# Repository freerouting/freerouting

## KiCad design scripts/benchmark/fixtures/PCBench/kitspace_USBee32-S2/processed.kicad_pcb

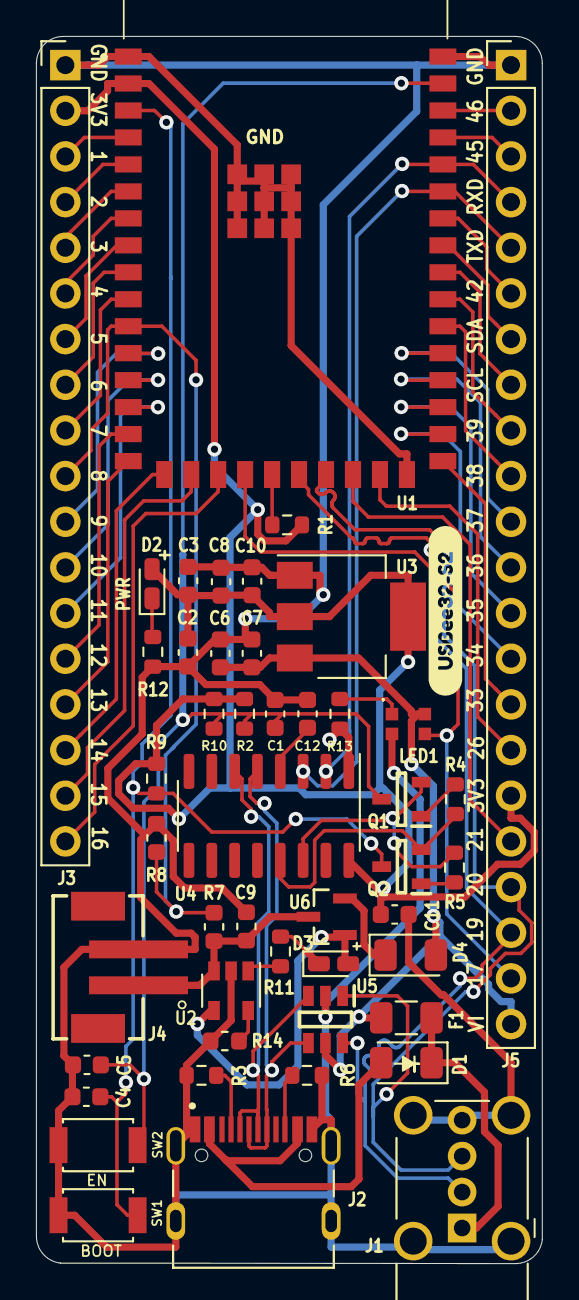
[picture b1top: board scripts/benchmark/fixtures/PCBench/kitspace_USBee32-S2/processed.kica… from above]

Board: 4 copper layers, 28.1 x 68.3 mm, 49 parts (1 on the bottom side), 59 nets.

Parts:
C1, C2, C4, C5, C7, C10, C11, C12: 0.1uF; C_0603_1608Metric
C3, C9: 10uF; C_0603_1608Metric
C6: 10 uF; C_0603_1608Metric
C8: 22 uF; C_0603_1608Metric
D1, D4: 1N5819; D_1206_3216Metric
D2, D3: LED; LED_0603_1608Metric_Castellated
F1: Polyfuse_Small; Fuse_1206_3216Metric
J1: USB_A; USB_A_Wuerth_614004134726_Horizontal
J2: TYPE-C-31-M-12; HRO_TYPE-C-31-M-12
J3: Conn_01x18_Male; PinHeader_1x18_P2.54mm_Vertical
J4: B2B-PH-SM4-TB(LF)(SN); JST_B2B-PH-SM4-TB(LF)(SN)
J5: Conn_01x22_Male; PinHeader_1x22_P2.54mm_Vertical
LED1: WS2812B-2020; WS2812B2020
Q1, Q2: MMBT8050
R1, R2, R4, R5, R9, R10: 10K; R_0603_1608Metric
R3, R6: 5.1K; R_0603_1608Metric
R7, R8: 100k; R_0603_1608Metric
R11, R12, R13: 1k; R_0603_1608Metric
R14: 4.7k; R_0603_1608Metric
SW1, SW2: SW_Push; tactile_smd_switch
U1: ESP32-S2-WROOM-ESP32-S2-WROOM; ESP32S2WROOMM22S2H3200PH3Q0
U2: MCP73831-2-OT; SOT-23-5
U3: AMS1117-3.3; SOT-223-3_TabPin2
U4: CH340C; SOIC-16_3.9x9.9mm_P1.27mm
U5: IP4220CZ6; SOP95P275X110-6N
U6: DMP2305U-7; SOT103P240X110-3N
svg2mod, svg2mod_2: G***; label

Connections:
+3V3: C2.1, C3.1, C8.2, C10.2, C11.1, D2.2, J3.2, J5.17, R1.1, R2.1, R9.2, R10.2, U1.2, U3.2, U4.16
+BATT: C9.1, J4.1, R7.1, U2.3, U6.3
/CC1: J2.A5, R3.1
/CC2: J2.B5, R6.1
/CHIP_PU: C1.1, C5.2, Q1.3, R2.2, R10.1, SW2.2, U1.41
/D1+: J1.3, J5.19, U1.23, U5.1
/D1-: J1.2, J5.20, U1.22, U5.6
/DN1: J2.A7, J2.B7, U4.6, U5.3
/DP1: J2.A6, J2.B6, U4.5, U5.4
/GPIO_0: C4.2, Q2.3, R9.1, SW1.2, U1.3
/GPIO_1: J3.3, U1.4
/GPIO_2: J3.4, U1.5
/GPIO_3: J3.5, U1.6
/GPIO_4: J3.6, U1.7
/GPIO_5: J3.7, U1.8
/GPIO_6: J3.8, U1.9
/GPIO_7: J3.9, U1.10
/GPIO_8: J3.10, R7.2, R8.1, U1.11
/GPIO_9: J3.11, U1.12
/GPIO_10: J3.12, U1.13
/GPIO_11: J3.13, U1.14
/GPIO_12: J3.14, U1.15
/GPIO_13: J3.15, U1.16
/GPIO_14: J3.16, U1.17
/GPIO_15: J3.17, U1.18
/GPIO_16: J3.18, U1.19
/GPIO_17: J5.21, LED1.3, U1.20
/GPIO_18: R1.2, U1.21
/GPIO_21: J5.18, U1.24
/GPIO_26: J5.16, U1.25
/GPIO_33: J5.15, U1.27
/GPIO_34: J5.14, U1.28
/GPIO_35: J5.13, U1.29
/GPIO_36: J5.12, U1.30
/GPIO_37: J5.11, U1.31
/GPIO_38: J5.10, U1.32
/GPIO_39: J5.9, U1.33
/GPIO_40: J5.8, U1.34
/GPIO_41: J5.7, U1.35
/GPIO_42: J5.6, U1.36
/GPIO_45: J5.3, U1.39
/GPIO_46: J5.2, U1.40
/RXD0: J5.4, U1.38, U4.2
/TXD0: J5.5, U1.37, U4.3
/VBUSA: D1.1, F1.2, J1.1
/VBUSC: D1.2, J2.A4B9, J2.B4A9
/VI: C6.2, C7.2, D3.2, D4.2, F1.1, J5.22, LED1.4, U2.4, U3.3, U5.5, U6.1
/~DTR: Q2.2, R4.1, U4.13
/~RTS: Q1.2, R5.1, U4.14
GND: C1.2, C2.2, C3.2, C4.1, C5.1, C6.1, C7.1, C8.1, C9.2, C10.1, C11.2, C12.2, J1.4, J1.5, J2.A1B12, J2.B1A12, J2.S1, J2.S2, J2.S3, J2.S4, J3.1, J4.2, J5.1, LED1.2, R3.2, R6.2, R8.2, R12.2, R13.2, R14.2, SW1.1, SW2.1, U1.1, U1.26, U1.42, U1.43, U1.44, U1.45, U1.46, U1.47, U1.48, U1.49, U1.50, U1.51, U2.2, U3.1, U4.1, U5.2
unnamed: C12.1, U4.4
unnamed: D2.1, R12.1
unnamed: D3.1, R11.1
unnamed: D4.1, U6.2
unnamed: LED1.1, R13.1
unnamed: Q1.1, R4.2
unnamed: Q2.1, R5.2
unnamed: R11.2, U2.1
unnamed: R14.1, U2.5

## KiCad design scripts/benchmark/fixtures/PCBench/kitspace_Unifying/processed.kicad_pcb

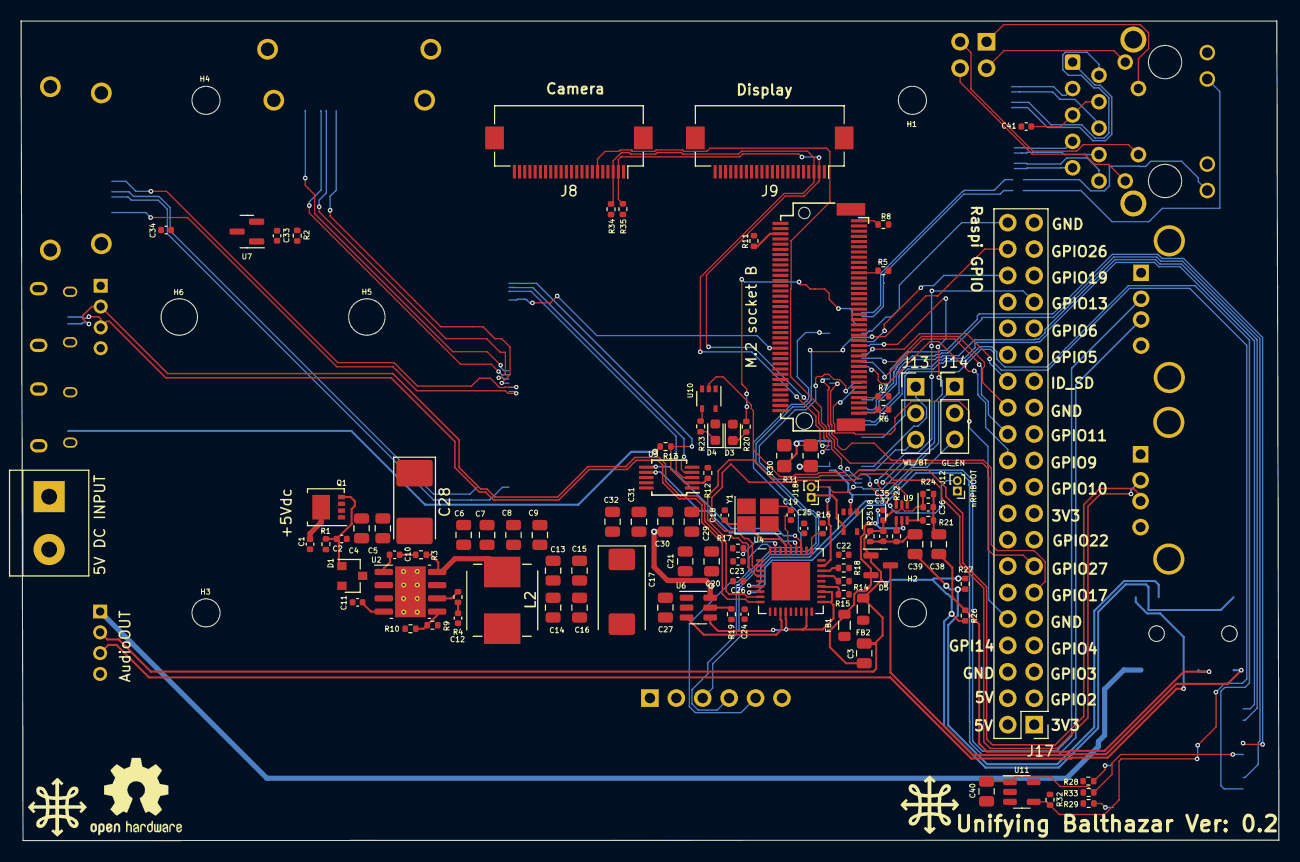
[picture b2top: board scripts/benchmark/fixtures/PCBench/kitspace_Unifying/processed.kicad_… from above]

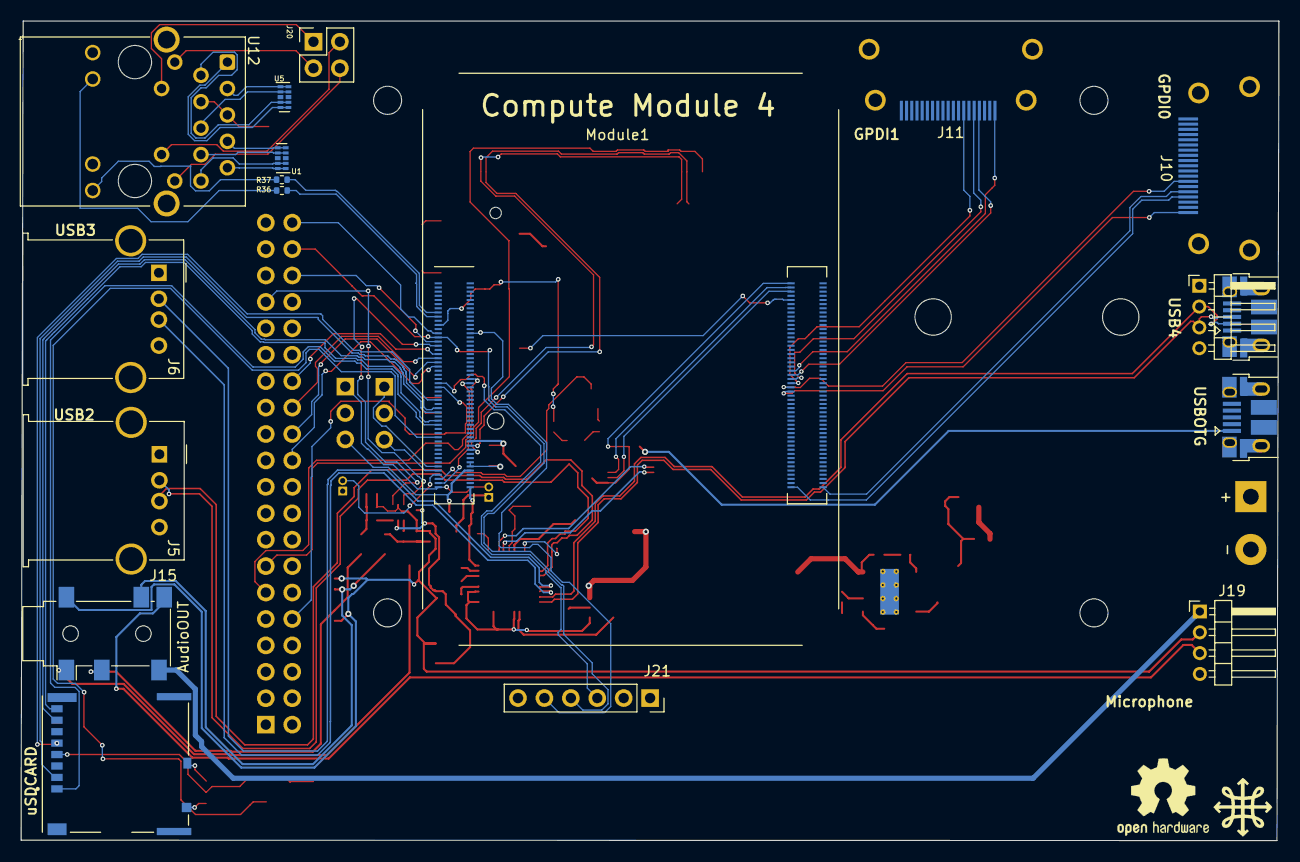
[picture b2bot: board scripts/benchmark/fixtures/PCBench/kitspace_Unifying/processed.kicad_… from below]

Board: 2 copper layers, 120.9 x 78.8 mm, 131 parts (20 on the bottom side), 113 nets.

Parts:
C1: 100n 50v; C_0402_1005Metric
C2, C10, C11, C22, C23, C24, C25, C26, C33, C34, C41: 100n; C_0402_1005Metric
C3, C13, C14, C15, C16, C20, C21, C27, C29, C30, C31, C32, C40: 10u; C_0805_2012Metric
C4, C5, C6, C7, C8, C9: 10u 10v; C_0805_2012Metric
C12: 1.2nF; C_0402_1005Metric
C17: 100uF; CP_EIA-7343-31_Kemet-D
C18, C19: 27pF; C_0402_1005Metric
C28: 100uF; CP_EIA-7132-20_AVX-U
C35, C36, C37: 100n 6.3; C_0402_1005Metric
C38, C39: 47u 6.3; C_0805_2012Metric
D1: MMBZ5242BLT3G; D_SOT-23_ANK
D3: LED Green; LED_0603_1608Metric
D4: LED Red; LED_0603_1608Metric
D5: BAV99; SOT-23
FB1, FB2: FerriteBead; L_0805_2012Metric
G1, G2, G3: LOGO; balthazar-logo
H1, H2, H3, H4: MountingHole; MountingHole_2.7mm_M2.5
H5, H6: M.2 Hole; M.2Hole_3.5mm
J1: Conn_01x02; TerminalBlock_bornier-2_P5.08mm
J2: Bus_M.2_Socket_B; Conn_TE-M.2-0.5-67P-doublesided
J3: USB_OTG; USB_Micro-B_EDAC_UCON00686
J4: Conn_01x04_Male; PinHeader_1x04_P2.00mm_Horizontal
J5, J6: USB_A; USB_A_Molex_67643_Horizontal
J7: USB_MICRO; USB_Micro-B_EDAC_UCON00686
J8, J9: Conn_01x22_Female; Hirose_FH12-22S-0.5SH_1x22-1MP_P0.50mm_Horizontal
J10: GPDI0; CONN-10029449-111RLF
J11: GPDI1; CONN-10029449-111RLF
J12: nRpiBoot; PinHeader_1x02_P1.00mm_Vertical
J13, J14: Conn_01x03; PinHeader_1x03_P2.54mm_Vertical
J15: AudioOUT; Jack_3.5mm_PJ311_Horizontal
J16: Micro_SD_Card_Det; SDCARD_MOLEX_503398-1892
J17: THD-20-R; PinHeader_2x20_P2.54mm_Vertical
J18: GLOBAL_EN; PinHeader_1x02_P1.00mm_Vertical
J19: AudioAMP; PinHeader_1x04_P2.00mm_Horizontal
J20: THD-02-R; PinHeader_2x02_P2.54mm_Vertical
J21: MIC; PinSocket_1x06_P2.54mm_Vertical
L2: SRN6045TA-3R3Y (3.3uH); L_Bourns_SRP7028A_7.3x6.6mm
Module1: ComputeModule4; Raspberry-Pi-4-Compute-Module-noholes
Q1: DMP3013SFV-7; Diodes_PowerDI3333-8
R1, R4, R17, R32: 12K 1%; R_0402_1005Metric
R2, R33: DNP; R_0402_1005Metric
R3: 10R; R_0402_1005Metric
R5, R6, R7, R8, R28, R29: nf; R_0402_1005Metric
R9: 47K 1%; R_0402_1005Metric
R10, R19: 15K 1%; R_0402_1005Metric
R11: 12K; R_0402_1005Metric
R12, R13: 2.2K 1%; R_0402_1005Metric
R14, R15, R16, R18: 36K 1%; R_0402_1005Metric
R20, R23: 1k; R_0402_1005Metric
R21, R22: 220; R_0402_1005Metric
R24, R25: 100; R_0402_1005Metric
R26, R27: 1K8; R_0402_1005Metric
R30: 0R; R_0805_2012Metric_Pad1.20x1.40mm_HandSolder
R31: nf; R_0805_2012Metric_Pad1.20x1.40mm_HandSolder
R34, R35: 4K7; R_0402_1005Metric
R36, R37: 470R; R_0402_1005Metric
REF1: OSHW-Logo2_9.8x8mm_SilkScreen
U1, U5: TPD4EUSB30; USON-10_2.5x1.0mm_P0.5mm
U2: AP64501SP-13; SOIC-8-1EP_3.9x4.9mm_P1.27mm_EP2.95x4.9mm_Mask2.71x3.4mm_Th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
U3: FSUSB42MUX; MSOP-10_3x3mm_P0.5mm
U4: USB2514B-I/M2; QFN-36-1EP_6x6mm_P0.5mm_EP3.7x3.7mm
U6: AP22653W6; SOT-23-6
U7: RT9742SNGV; SOT-23
U8, U10: 74LVC1G07SE-7; SOT-353_SC-70-5
U9: NC7WZ16; SC-88-6_2x2.1mm
U11: RT9742GGJ5; SOT-23-5
U12: MagJack-A70-112-331N126; TRJG0926HENL
Y1: 24MHz; Crystal_SMD_EuroQuartz_X22-4Pin_2.5x2.0mm_HandSoldering

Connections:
/CM4_GPIO (GPIO, SDCARD)/+1.8v: Module1.88, Module1.90, R31.1
/CM4_GPIO (GPIO, SDCARD)/AUDIO_L: C38.2, J15.3, R26.2
/CM4_GPIO (GPIO, SDCARD)/AUDIO_R: C39.2, J15.4, R27.2
/CM4_GPIO (GPIO, SDCARD)/BCLK: J21.3, Module1.49
/CM4_GPIO (GPIO, SDCARD)/BT_nDis: J13.3, Module1.91
/CM4_GPIO (GPIO, SDCARD)/DOUT: J17.38, J21.4, Module1.27
/CM4_GPIO (GPIO, SDCARD)/ETH_LEDG: Module1.17, R36.2
/CM4_GPIO (GPIO, SDCARD)/ETH_LEDY: Module1.15, R37.2
/CM4_GPIO (GPIO, SDCARD)/GLOBAL_EN: J14.1, J18.2, Module1.99
/CM4_GPIO (GPIO, SDCARD)/GPIO7: J17.26, Module1.37
/CM4_GPIO (GPIO, SDCARD)/GPIO8: J17.24, Module1.39
/CM4_GPIO (GPIO, SDCARD)/GPIO12: Module1.31, U9.1
/CM4_GPIO (GPIO, SDCARD)/GPIO13: J17.33, U9.3
/CM4_GPIO (GPIO, SDCARD)/GPIO15: J17.10, Module1.51
/CM4_GPIO (GPIO, SDCARD)/GPIO16: J17.36, Module1.29
/CM4_GPIO (GPIO, SDCARD)/GPIO17: J17.11, Module1.50
/CM4_GPIO (GPIO, SDCARD)/GPIO21: J17.40, Module1.25
/CM4_GPIO (GPIO, SDCARD)/GPIO25: J17.22, Module1.41
/CM4_GPIO (GPIO, SDCARD)/GPIO27: J17.13, Module1.48
/CM4_GPIO (GPIO, SDCARD)/GPIO_VREF: Module1.78, R30.2, R31.2
/CM4_GPIO (GPIO, SDCARD)/ID_SC: J17.28, Module1.35
/CM4_GPIO (GPIO, SDCARD)/LRCL: J21.5, Module1.26
/CM4_GPIO (GPIO, SDCARD)/RUN_PG: J14.3, Module1.92, U8.2
/CM4_GPIO (GPIO, SDCARD)/SD_DAT0: J16.7, Module1.63
/CM4_GPIO (GPIO, SDCARD)/SD_DAT1: J16.8, Module1.67
/CM4_GPIO (GPIO, SDCARD)/SD_DAT2: J16.1, Module1.69
/CM4_GPIO (GPIO, SDCARD)/SD_DAT3: J16.2, Module1.61
/CM4_GPIO (GPIO, SDCARD)/SD_PWR: C40.1, J16.4, R33.1, U11.1
/CM4_GPIO (GPIO, SDCARD)/SD_PWR_ON: Module1.75, R32.2, U11.4
/CM4_GPIO (GPIO, SDCARD)/TR0_TAP: J20.3, U12.11
/CM4_GPIO (GPIO, SDCARD)/TR1_TAP: J20.1, U12.12
/CM4_GPIO (GPIO, SDCARD)/TR2_TAP: J20.2, U12.13
/CM4_GPIO (GPIO, SDCARD)/TR3_TAP: J20.4, U12.14
/CM4_GPIO (GPIO, SDCARD)/TRD0_N: U5.4, U5.7, U12.2
/CM4_GPIO (GPIO, SDCARD)/TRD0_P: U5.5, U5.6, U12.1
/CM4_GPIO (GPIO, SDCARD)/TRD1_N: U5.2, U5.9, U12.6
/CM4_GPIO (GPIO, SDCARD)/TRD1_P: U5.1, U5.10, U12.3
/CM4_GPIO (GPIO, SDCARD)/TRD2_N: U1.4, U1.7, U12.8
/CM4_GPIO (GPIO, SDCARD)/TRD2_P: U1.5, U1.6, U12.7
/CM4_GPIO (GPIO, SDCARD)/TRD3_N: U1.2, U1.9, U12.10
/CM4_GPIO (GPIO, SDCARD)/TRD3_P: U1.1, U1.10, U12.9
/CM4_GPIO (GPIO, SDCARD)/WL_nDis: J13.1, Module1.89
/CM4_GPIO (GPIO, SDCARD)/nPWR_LED: Module1.95, U10.2
/CM4_GPIO (GPIO, SDCARD)/nRPIBOOT: J12.2, Module1.93
/CM4_HighSpeed/CAM_GPIO: J8.6, Module1.97
/CM4_HighSpeed/HDMI1_CEC: J11.13, Module1.149
/CM4_HighSpeed/HDMI1_HOTPLUG: J11.19, Module1.143
/CM4_HighSpeed/HDMI1_SCL: J11.15, Module1.147
/CM4_HighSpeed/HDMI1_SDA: J11.16, Module1.145
/CM4_HighSpeed/SCL0: J8.3, J9.3, Module1.80, R34.2
/CM4_HighSpeed/SDA0: J8.2, J9.2, Module1.82, R35.2
/CM4_HighSpeed/USB2_N: Module1.103, U3.4
/CM4_HighSpeed/USB2_P: Module1.105, U3.3
/CM4_HighSpeed/USBOTG_ID: Module1.101, R12.1, R13.2, U3.2
/PCIE_nRST: J2.50, Module1.109
/USB2-HUB/HD2_N: J5.2, U4.3
/USB2-HUB/HD2_P: J5.3, U4.4
/USB2-HUB/HD3_N: J6.2, U4.6
/USB2-HUB/HD3_P: J6.3, U4.7
/USB2-HUB/HD4_N: J4.2, J7.2, U4.8
/USB2-HUB/HD4_P: J4.3, J7.3, U4.9
/USB2-HUB/PWR1: U4.12, U6.3
/USB2-HUB/USBH_N: U3.6, U4.30
/USB2-HUB/USBH_P: U3.7, U4.31
/USB2-HUB/VBUS: C30.1, U6.6
/USB2-HUB/nOCS1: U4.13, U4.17, U4.19, U4.21, U6.4
/nEXTRST: Module1.100, U4.26
HDMI0_CEC: J10.13, Module1.151
HDMI0_HOTPLUG: J10.19, Module1.153
HDMI0_SCL: J10.15, Module1.200
HDMI0_SDA: J10.16, Module1.199
unnamed: C10.1, R3.2
unnamed: C12.1, R4.2
unnamed: C36.1, C38.1, R21.2, R24.2
unnamed: C37.1, C39.1, R22.2, R25.2
unnamed: C2.2, D1.2, Q1.4, R1.1
unnamed: D3.1, R20.1
unnamed: D4.1, R23.1
unnamed: C3.1, C35.1, D5.2, FB1.2, U9.5
unnamed: D5.3, J15.1
unnamed: C3.2, C35.2, C36.2, C37.2, D5.1, FB2.1, J15.2, J19.2, R24.1, R25.1, R26.1, R27.1, U9.2
unnamed: C1.1, Q1.5
unnamed: J2.21, R5.2
unnamed: J2.69, R6.2
unnamed: J2.75, R7.2
unnamed: J2.1, R8.2
unnamed: J2.6, R11.1
unnamed: J3.1, R13.1
unnamed: J16.10, R28.2
unnamed: J16.9, R29.2
unnamed: J18.1, U8.4
unnamed: J15.6, J19.1
unnamed: J15.5, J19.3
unnamed: Module1.21, R20.2
unnamed: R23.2, U10.4
unnamed: C10.2, U2.1
unnamed: R4.1, U2.6
unnamed: R9.2, R10.1, U2.5
unnamed: C11.1, U2.4
unnamed: L2.1, R3.1, U2.8
unnamed: R18.1, U4.25
unnamed: R17.2, U4.35
unnamed: R14.1, U4.24
unnamed: R15.1, U4.22
unnamed: R16.1, U4.28
unnamed: C18.1, U4.33, Y1.1
unnamed: C19.1, U4.32, Y1.3
unnamed: R19.1, U6.5
unnamed: R21.1, U9.6
unnamed: R22.1, U9.4
unnamed: C41.1, U12.4, U12.5
unnamed: R36.1, U12.16
unnamed: R37.1, U12.18

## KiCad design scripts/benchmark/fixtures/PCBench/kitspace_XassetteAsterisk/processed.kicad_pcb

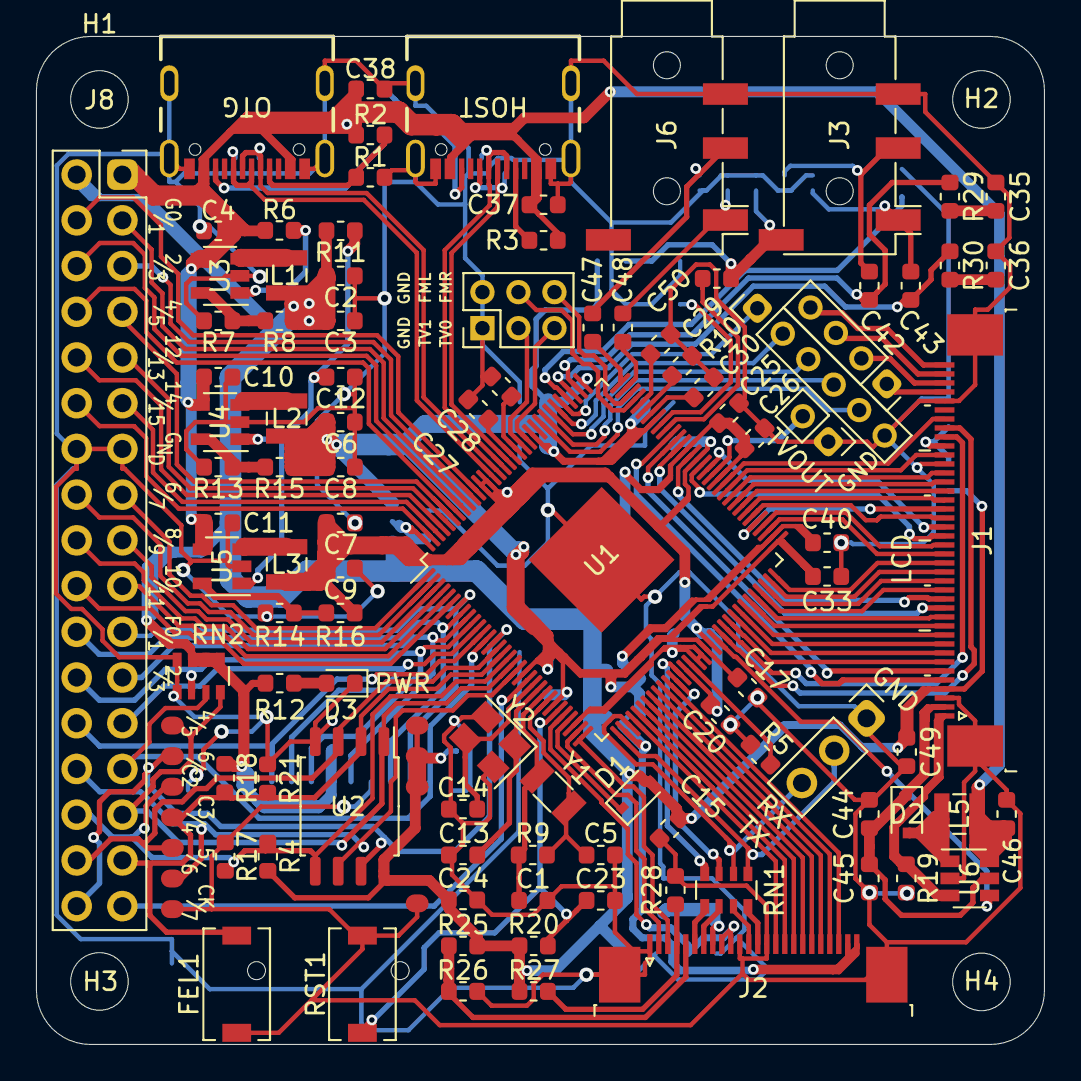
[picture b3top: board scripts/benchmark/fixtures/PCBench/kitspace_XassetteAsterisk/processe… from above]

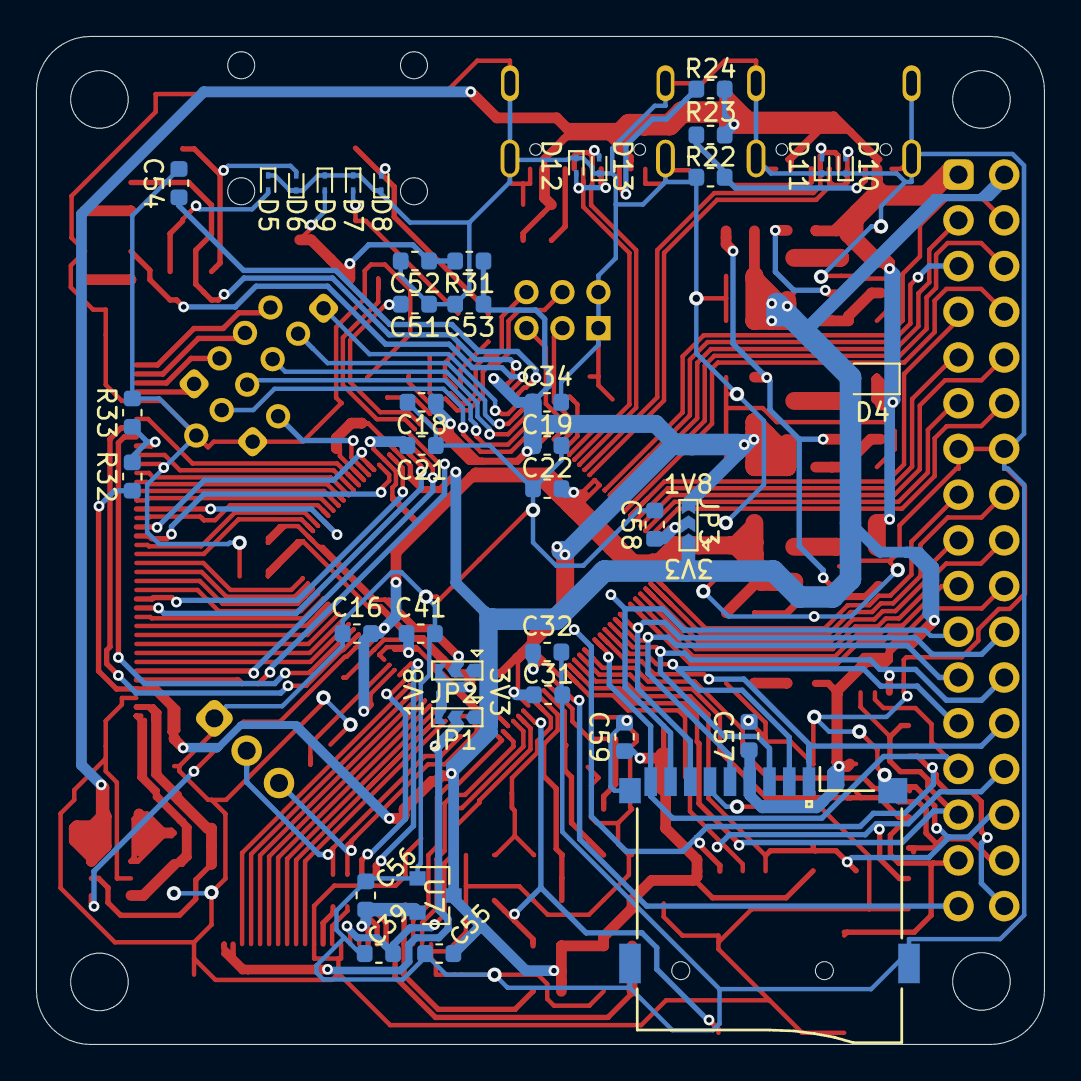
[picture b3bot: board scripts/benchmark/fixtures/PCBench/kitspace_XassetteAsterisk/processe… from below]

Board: 2 copper layers, 56.0 x 56.0 mm, 145 parts (41 on the bottom side), 151 nets.

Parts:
C1, C5, C13, C14: 18p; C_0603_1608Metric
C2, C4, C6, C7, C10, C11, C37, C38, C44, C46, C53, C55: 10u; C_0603_1608Metric
C3, C8, C9, C12, C15, C16, C17, C18, C19, C20, C21, C22, C23, C24, C25, C26, C31, C32, C33, C34, C35, C36, C39, C40, C41, C42, C43, C45, C47, C48, C49, C50, C51, C54, C56, C57, C58, C59: 0.1u; C_0603_1608Metric
C27, C28: 1u; C_0603_1608Metric
C29, C30: 0.47u; C_0603_1608Metric
C52: 33p; C_0603_1608Metric
D1, D2, D4: D; D_SOD-323
D3: LED; LED_0603_1608Metric
D5, D6, D7, D8, D9, D10, D11, D12, D13: ESD9B3.3ST5G; D_SOD-923
FEL1: SW_SPST; SW_SPST_EVQPE1
H1, H2, H3, H4: MountingHole; MountingHole_3.2mm_M3
H5: MountingHole_Pad; SolderWirePad_1x01_SMD_5x10mm
J1: Conn_01x40_MountingPin; TE_4-1734839-0_1x40-1MP_P0.5mm_Horizontal
J2: Conn_01x24_MountingPin; TE_2-1734839-4_1x24-1MP_P0.5mm_Horizontal
J3, J6: AudioJack4; Jack_3.5mm_PJ320D_Horizontal
J4, J5: USB4105-GF-A; GCT_USB4105-GF-A
J7: Conn_01x04; PinSocket_1x04_P2.00mm_Vertical
J8: Conn_02x17_Odd_Even; PinSocket_2x17_P2.54mm_Vertical
J9: Conn_01x06; PinHeader_1x06_P2.00mm_Vertical
J10: Conn_02x03_Odd_Even; PinHeader_2x03_P2.00mm_Vertical
J11: Conn_01x02; PinHeader_1x02_P2.00mm_Vertical
J12: Conn_01x03; PinHeader_1x03_P2.54mm_Vertical
J13: RTL8189FTV_Mod; 8189Mod
JP1, JP2, JP3: Jumper_3_Open; SolderJumper-3_P2.0mm_Open_TrianglePad1.0x1.5mm
L1, L2, L3: 2.2u; L_Wuerth_MAPI-2510
L5: 10u; L_Wuerth_MAPI-2510
R1, R2, R3, R12, R22, R23, R24: 5.1k; R_0603_1608Metric
R4, R11, R17, R18, R21, R25, R26, R27, R28, R32, R33: 10k; R_0603_1608Metric
R5: 240; R_0603_1608Metric
R6: 1k; R_0603_1608Metric
R7: 15k; R_0603_1608Metric
R8: 68k; R_0603_1608Metric
R9: 10M; R_0603_1608Metric
R10: 0; R_0603_1608Metric
R13, R16, R20: 100k; R_0603_1608Metric
R14, R15: 200k; R_0603_1608Metric
R19, R29, R30: 2R2; R_0603_1608Metric
R31: 2.2k; R_0603_1608Metric
RN1, RN2: R_Pack04; R_Array_Convex_4x0603
RST1: SW_SPST; SW_SPST_EVQPE1
Ref**: Val**; rvlogo_inv
U1: F133; LQFP-128_14x14mm_P0.4mm
U2: W25Q32JVSS; SOIC-8_5.23x5.23mm_P1.27mm
U3, U4, U5: SY8089AAAC; SOT-23-5
U6: SY7201ABC; SOT-23-6
U7: XC6206PxxxMR; SOT-23
XS1: uSD_SMD; Conn_uSDcard
Y1: Crystal; Crystal_SMD_3215-2Pin_3.2x1.5mm
Y2: 24M; Crystal_SMD_3225-4Pin_3.2x2.5mm

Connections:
+1V8: C6.1, C8.1, C17.1, C18.1, C19.1, C31.1, C32.1, C33.1, C34.1, C53.1, JP1.3, JP2.3, JP3.3, L2.1, R15.1, R31.1, U1.20, U1.26, U1.50, U1.65, U1.89, U1.97, U1.107
+3V3: C2.1, C3.1, C15.1, C24.1, C25.1, C26.1, C49.1, C55.2, C57.1, C59.1, D1.2, D4.2, J1.4, J8.2, J13.11, J13.12, J13.13, JP1.1, JP2.1, JP3.1, L1.1, R4.1, R8.1, R11.1, R12.1, R18.1, R20.1, R25.1, R27.1, R32.1, RN2.1, RN2.2, RN2.3, U1.77, U1.83, U2.8, U7.3, XS1.4
+5V: C4.1, C10.1, C11.1, C37.1, C38.1, C46.1, D4.1, J4.A4_B9, J4.B4_A9, J5.A4_B9, J5.B4_A9, J8.1, L5.1, R2.1, R3.1, R6.1, R23.1, R24.1, U3.4, U4.4, U5.4, U6.6
/CLKO: J8.33, U1.21
/CSI-AVDD: C39.1, J2.9, J2.10, U1.28
/CSI-DVDD: C56.1, J2.8, U7.2
/CSI-IOVDD: J2.23, J2.24, JP1.2, U1.34
/CSI-PWDN: J2.5, R25.2, R26.1
/CSI-RST#: J2.4, R27.2, R28.1
/DISP: J1.31, R32.2, R33.1
/DXIN: C13.2, U1.23, Y2.1
/DXOUT: C14.1, U1.22, Y2.3
/FMINL: J10.6, U1.94
/FMINR: J10.4, U1.93
/GPADC0: J9.1, U1.101
/HPOUTFB: C54.1, U1.100
/HPOUTL: C43.2, R30.2, U1.99
/HPOUTR: C42.2, R29.2, U1.98
/HS_MIC: C50.2, C52.1, D9.2, J3.S, R31.2
/LCD0-CLK: J1.30, U1.75
/LCD0-D0: J1.5, U1.86
/LCD0-D1: J1.6, U1.85
/LCD0-D2: J1.7, U1.55
/LCD0-D3: J1.8, U1.56
/LCD0-D4: J1.9, U1.57
/LCD0-D5: J1.10, U1.58
/LCD0-D6: J1.11, U1.59
/LCD0-D7: J1.12, U1.60
/LCD0-D8: J1.13, U1.84
/LCD0-D9: J1.14, U1.82
/LCD0-D10: J1.15, U1.61
/LCD0-D11: J1.16, U1.62
/LCD0-D12: J1.17, U1.63
/LCD0-D13: J1.18, U1.64
/LCD0-D14: J1.19, U1.67
/LCD0-D15: J1.20, U1.68
/LCD0-D16: J1.21, U1.80
/LCD0-D17: J1.22, U1.79
/LCD0-D18: J1.23, U1.70
/LCD0-D19: J1.24, U1.69
/LCD0-D20: J1.25, U1.71
/LCD0-D21: J1.26, U1.72
/LCD0-D22: J1.27, U1.73
/LCD0-D23: J1.28, U1.74
/LCD0-DE: J1.34, U1.76
/LCD0-HSYNC: J1.32, U1.54
/LCD0-VSYNC: J1.33, U1.53
/LCD0_PWM: U1.52, U6.4
/LCD_A: C44.1, C45.1, D2.1, J1.2, U6.5
/LCD_K: J1.1, R19.1, U6.3
/LDOB-OUT: C41.1, U1.30, U1.48, U1.49
/LINEL: C47.2, U1.96
/LINER: C48.2, U1.95
/MIC3N: C51.1, U1.88
/MIC3P: C50.1, U1.87
/NCSI0-D0: J2.22, U1.43
/NCSI0-D1: J2.21, U1.42
/NCSI0-D2: J2.20, U1.41
/NCSI0-D3: J2.19, U1.40
/NCSI0-D4: J2.18, U1.39
/NCSI0-D5: J2.17, U1.38
/NCSI0-D6: J2.16, U1.37
/NCSI0-D7: J2.15, U1.36
/NCSI0-HSYNC: RN1.7, U1.44
/NCSI0-MCLK: J12.2, RN1.5, U1.33
/NCSI0-PCLK: J12.3, RN1.6, U1.35
/NCSI0-VSYNC: RN1.8, U1.45
/PC2: J8.28, J13.6, U1.19, U2.6
/PC3: J8.29, J13.1, RN2.8, U1.18, U2.1
/PC4: J8.30, J13.3, R4.2, R17.1, U1.17, U2.5
/PC5: FEL1.2, J8.31, J13.4, R18.2, R21.1, U1.16, U2.2
/PC6: J8.32, J13.5, U1.15, U2.3
/PC7: J8.34, J13.2, U1.14, U2.7
/PF0: J8.21, U1.7, XS1.8
/PF1: J8.22, U1.8, XS1.7
/PF2: J8.23, U1.9, XS1.5
/PF3: J8.24, RN2.6, U1.10, XS1.3
/PF4: J8.25, U1.11, XS1.2
/PF5: J8.26, U1.12, XS1.1
/PF6: J8.27, RN2.7, U1.13, XS1.9
/PG0: J8.3, U1.120
/PG1: J8.4, U1.118
/PG2: J8.5, U1.119
/PG3: J8.6, U1.121
/PG4: J8.7, U1.123
/PG5: J8.8, U1.122
/PG6: J8.15, U1.1
/PG7: J8.16, U1.2
/PG8: J8.17, U1.3
/PG9: J8.18, U1.4
/PG10: J8.19, U1.5
/PG11: J8.20, U1.6
/PG12: J8.9, U1.124
/PG13: J8.10, U1.125
/PG14: J8.11, U1.126
/PG15: J8.12, U1.127
/RST: C23.1, R20.2, RST1.2, U1.27
/TP_X1: J9.2, U1.102
/TP_X2: J9.3, U1.103
/TP_Y1: J9.4, U1.104
/TP_Y2: J9.5, U1.105
/TVIN0: J10.5, U1.108
/TVIN1: J10.3, U1.109
/TVOUT: J11.2, U1.78
/TWI2-SCK: J2.3, U1.32
/TWI2-SDA: J2.2, U1.31
/USB0_N: D11.2, J4.A7, J4.B7, U1.114
/USB0_P: D10.2, J4.A6, J4.B6, U1.115
/USB1_N: D13.2, J5.A7, J5.B7, U1.113
/USB1_P: D12.2, J5.A6, J5.B6, U1.112
/VCC_PD: C40.2, JP2.2, U1.66
/VCC_PG: C58.2, JP3.2, U1.128
/VDD-CORE: C7.1, C9.1, C16.1, C20.1, C21.1, C22.1, L3.1, R16.1, U1.46, U1.51, U1.81, U1.116, U1.117
GND: C1.2, C2.2, C3.2, C4.2, C5.2, C6.2, C7.2, C8.2, C9.2, C10.2, C11.2, C12.2, C13.1, C14.2, C15.2, C16.2, C17.2, C18.2, C19.2, C20.2, C21.2, C22.2, C23.2, C24.2, C25.2, C26.2, C27.2, C28.2, C29.1, C30.1, C31.2, C32.2, C33.2, C34.2, C35.1, C36.1, C37.2, C38.2, C39.2, C40.1, C41.2, C44.2, C45.2, C46.2, C49.2, C51.2, C52.2, C53.2, C54.2, C55.1, C56.2, C57.2, C58.1, C59.2, D3.1, D5.1, D6.1, D7.1, D8.1, D9.1, D10.1, D11.1, D12.1, D13.1, FEL1.1, H5.1, J1.3, J1.29, J1.36, J1.MP, J2.1, J2.11, J2.14, J2.MP, J3.R2, J4.A1_B12, J4.B1_A12, J4.S1, J4.S2, J4.S3, J4.S4, J5.A1_B12, J5.B1_A12, J5.S1, J5.S2, J5.S3, J5.S4, J6.R2, J8.13, J8.14, J9.6, J10.1, J10.2, J11.1, J12.1, J13.7, J13.8, R1.2, R5.2, R7.2, R10.1, R13.2, R14.2, R17.2, R19.2, R21.2, R22.2, R26.2, R28.2, R33.2, RN2.4, RN2.5, RST1.1, U2.4, U3.2, U4.2, U5.2, U6.2, U7.1, XS1.6, Y2.2, Y2.4
unnamed: C1.1, R9.1, U1.24, Y1.1
unnamed: C5.1, R9.2, U1.25, Y1.2
unnamed: C12.1, R11.2, U4.1, U5.1
unnamed: C27.1, U1.111
unnamed: C28.1, U1.110
unnamed: C29.2, U1.92
unnamed: C30.2, U1.90
unnamed: C35.2, R29.1
unnamed: C36.2, R30.1
unnamed: C42.1, D6.2, J3.R1
unnamed: C43.1, D5.2, J3.T
unnamed: C47.1, D8.2, J6.R1
unnamed: C48.1, D7.2, J6.T
unnamed: D1.1, U1.29
unnamed: D2.2, L5.2, U6.1
unnamed: D3.2, R12.2
unnamed: J1.37, J7.1
unnamed: J1.38, J7.2
unnamed: J1.39, J7.3
unnamed: J1.40, J7.4
unnamed: J2.6, RN1.1
unnamed: J2.7, RN1.2
unnamed: J2.12, RN1.3
unnamed: J2.13, RN1.4
unnamed: J4.A5, R1.1, R2.2
unnamed: J4.B5, R22.1, R23.2
unnamed: J5.A5, R3.2
unnamed: J5.B5, R24.2
unnamed: L1.2, U3.3
unnamed: L2.2, U4.3
unnamed: L3.2, U5.3
unnamed: R5.1, U1.47
unnamed: R6.2, U3.1
unnamed: R7.1, R8.2, U3.5
unnamed: R10.2, U1.91
unnamed: R13.1, R15.2, U4.5
unnamed: R14.1, R16.2, U5.5
